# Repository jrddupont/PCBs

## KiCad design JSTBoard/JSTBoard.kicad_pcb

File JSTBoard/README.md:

This board connects up to 30 JST ZR (1.5mm pitch) or PH (2.0mm pitch) connectors in parallel in 6 groups of 5, the board can be snapped apart into smaller boards if desired.   
The standard use case is to connect four solar panels in parallel to a single output connector.    

JST ZR (1.5mm): https://www.digikey.com/en/products/detail/jst-sales-america-inc/B2B-ZR/926564  
JST PH (2.0mm): https://www.digikey.com/en/products/detail/jst-sales-america-inc/B2B-PH-K-S/926611    
  
I have included an STL for a 3D printed jig to help solder the 1.5mm JST connectors to the board.

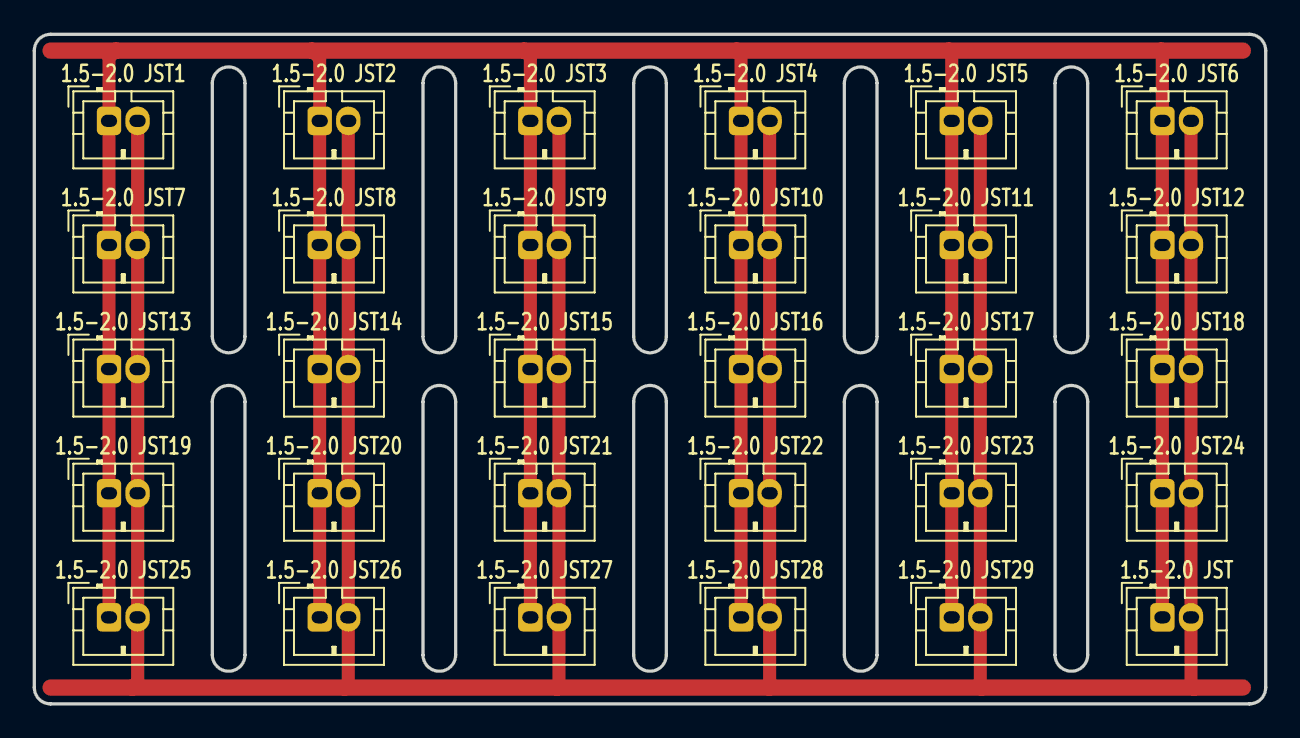
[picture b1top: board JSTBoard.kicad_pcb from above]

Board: 2 copper layers, 75.4 x 41.0 mm, 30 parts (0 on the bottom side), 2 nets.

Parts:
1.5-2.0 JST, 1.5-2.0 JST1, 1.5-2.0 JST2, 1.5-2.0 JST3, 1.5-2.0 JST4, 1.5-2.0 JST5, 1.5-2.0 JST6, 1.5-2.0 JST7, 1.5-2.0 JST8, 1.5-2.0 JST9, 1.5-2.0 JST10, 1.5-2.0 JST11, 1.5-2.0 JST12, 1.5-2.0 JST13, 1.5-2.0 JST14, 1.5-2.0 JST15, 1.5-2.0 JST16, 1.5-2.0 JST17, 1.5-2.0 JST18, 1.5-2.0 JST19, 1.5-2.0 JST20, 1.5-2.0 JST21, 1.5-2.0 JST22, 1.5-2.0 JST23, 1.5-2.0 JST24, 1.5-2.0 JST25, 1.5-2.0 JST26, 1.5-2.0 JST27, 1.5-2.0 JST28, 1.5-2.0 JST29: JST_Custom_Cursed

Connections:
unnamed: 1.5-2.0 JST1.1, 1.5-2.0 JST2.1, 1.5-2.0 JST3.1, 1.5-2.0 JST4.1, 1.5-2.0 JST5.1, 1.5-2.0 JST6.1
unnamed: 1.5-2.0 JST.2, 1.5-2.0 JST25.2, 1.5-2.0 JST26.2, 1.5-2.0 JST27.2, 1.5-2.0 JST28.2, 1.5-2.0 JST29.2

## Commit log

2025-09-14 Added JST Header Board
2025-09-14 Added Jig
